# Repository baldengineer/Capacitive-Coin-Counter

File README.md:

## Capacitive Coin Counter
Project for a video to make use of an automatic coin detector. It can be programmed to identify up to 4 coins.

### Code
Code for the Arduino and MSP430

### Electronics
Schematics for the 12V boost regulator and the breadboard

### Enclosure
Laser cut and 3d printing files to build the box.

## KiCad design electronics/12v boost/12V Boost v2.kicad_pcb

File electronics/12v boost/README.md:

A ~3V to 12V or 24V boost converter. The resistors listed in the BOM are for 12V. Change the R3 to 56K to get 24V out. Regulator can handle about 50 mA continous and peaks up to 500 mA. Based on the Microchip MCP1661. You can order the board from OSHPark: https://oshpark.com/shared_projects/hU1dj3Ux

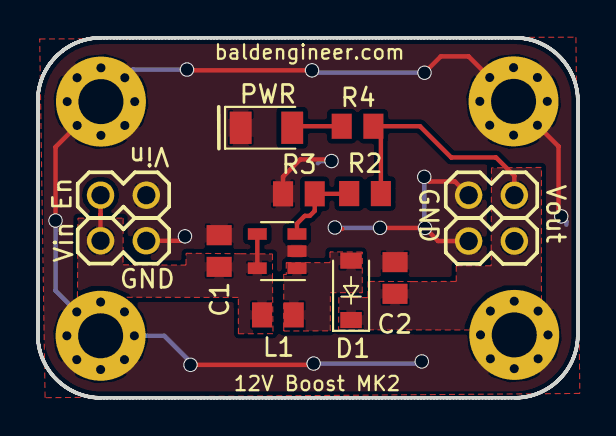
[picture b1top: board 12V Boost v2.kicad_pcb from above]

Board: 2 copper layers, 30.0 x 20.0 mm, 17 parts (0 on the bottom side), 6 nets.

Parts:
C1, C2: 10u; C_0805_2012Metric
D1: MBR0540; D_SOD-123
D2: PWR; LED_1206_3216Metric
JP1, JP2, JP3, JP4: M02; 1X02
L1: 4.7u; L_0805_2012Metric
MK1, MK2, MK3, MK4: Mounting_Hole_PAD; MountingHole_2.5mm_Pad_Via
R2: 1.05M; R_0805_2012Metric
R3: 120k; R_0805_2012Metric
R4: 1k; R_0805_2012Metric
U1: MCP1661; SOT-23-5

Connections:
/FB: R2.2, R3.1, U1.3
/SW: D1.2, L1.2, U1.1
/Vin: C1.1, JP1.1, JP3.1, L1.1, U1.4, U1.5
/Vout: C2.1, D1.1, JP2.1, JP4.1, R2.1, R4.2
GND: C1.2, C2.2, D2.1, JP1.2, JP2.2, JP3.2, JP4.2, MK1.1, MK2.1, MK3.1, MK4.1, R3.2, U1.2
unnamed: D2.2, R4.1

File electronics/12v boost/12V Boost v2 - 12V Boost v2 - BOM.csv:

Ref,Qnty,Value,Cmp name,Description,Vendor
"C1, C2, ",2,10u,C,Unpolarized capacitor,
"D1, ",1,MBR0540,D_Schottky,Schottky diode,
"D2, ",1,PWR,LED,LED generic,
"L1, ",1,4.7u,L,Inductor,
"R2, ",1,1.05M,R,Resistor,
"R3, ",1,120k,R,Resistor,
"R4, ",1,1k,R,Resistor,
"U1, ",1,MCP1661,MCP1661,,

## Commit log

2018-08-08 Initial Commit
    More details to follow
